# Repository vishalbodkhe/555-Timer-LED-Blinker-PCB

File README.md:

# 555 Timer LED Blinker PCB

A 555 Timer based LED Blinker PCB designed using KiCad.

## Project Overview

This project is a simple LED blinker circuit using the NE555 timer IC in astable mode.

The complete PCB design workflow was performed using KiCad, including:

- Circuit schematic design
- Footprint assignment
- PCB component placement
- PCB routing
- Design Rule Check (DRC)
- 3D PCB verification
- Gerber file generation
- Drill file generation

## Components

| Reference | Component | Value |
|----------|-----------|-------|
| U1 | NE555 Timer IC | NE555D |
| R1 | Resistor | 1kΩ |
| R2 | Resistor | 10kΩ |
| R3 | Resistor | 330Ω |
| C1 | Capacitor | 10µF |
| C2 | Capacitor | 100nF |
| D1 | LED | LED |
| J1 | Screw Terminal | 2-Pin |

## Circuit

The NE555 timer is configured in astable mode to generate a continuous square-wave output.

The output of the 555 timer drives the LED through a 330Ω current-limiting resistor.

## Design Workflow

1. Schematic Design
2. Assign PCB Footprints
3. PCB Component Placement
4. PCB Routing
5. Design Rule Check
6. 3D PCB Verification
7. Gerber Generation
8. Drill File Generation

## PCB Design

The PCB was designed and routed using KiCad.

The board includes:

- 2-pin power input
- NE555 timer IC
- Timing resistor network
- Timing capacitors
- LED indicator
- Current limiting resistor
- Four mounting holes

## 3D PCB View

## Design Verification

- Schematic completed
- PCB layout completed
- PCB routing completed
- DRC completed successfully
- DRC Violations: 0
- Unconnected Items: 0
- 3D PCB model verified

## Gerber Files

Gerber files required for PCB fabrication are included in this repository.

Included fabrication files:

- Front Copper
- Back Copper
- Front Solder Mask
- Back Solder Mask
- Front Silkscreen
- Back Silkscreen
- Edge Cuts
- Drill Files

## Project Files

### KiCad Files

- `p2.kicad_sch` — Schematic
- `p2.kicad_pcb` — PCB Layout
- `p2.kicad_pro` — KiCad Project

### Manufacturing Files

- `p2-F_Cu.gbr`
- `p2-B_Cu.gbr`
- `p2-F_Mask.gbr`
- `p2-B_Mask.gbr`
- `p2-F_Silkscreen.gbr`
- `p2-B_Silkscreen.gbr`
- `p2-Edge_Cuts.gbr`
- `p2-PTH.drl`
- `p2-NPTH.drl`

## Tools Used

- KiCad
- PCB Editor
- Schematic Editor
- 3D Viewer
- Design Rules Checker
- Gerber Viewer

## Learning Outcomes

Through this project, I learned and practiced:

- PCB schematic creation
- Electronic component selection
- Footprint assignment
- PCB layout design
- Component placement
- PCB trace routing
- Ground plane / copper zone
- Design Rule Checking
- Gerber generation
- Drill file generation
- 3D PCB visualization

## Project Status

**Completed**

Schematic → PCB Layout → Routing → DRC → 3D Verification → Gerber Generation

## Author

**Vishal Bodkhe**

Electronics & Computer Engineering

## License

This project is created for educational and portfolio purposes.

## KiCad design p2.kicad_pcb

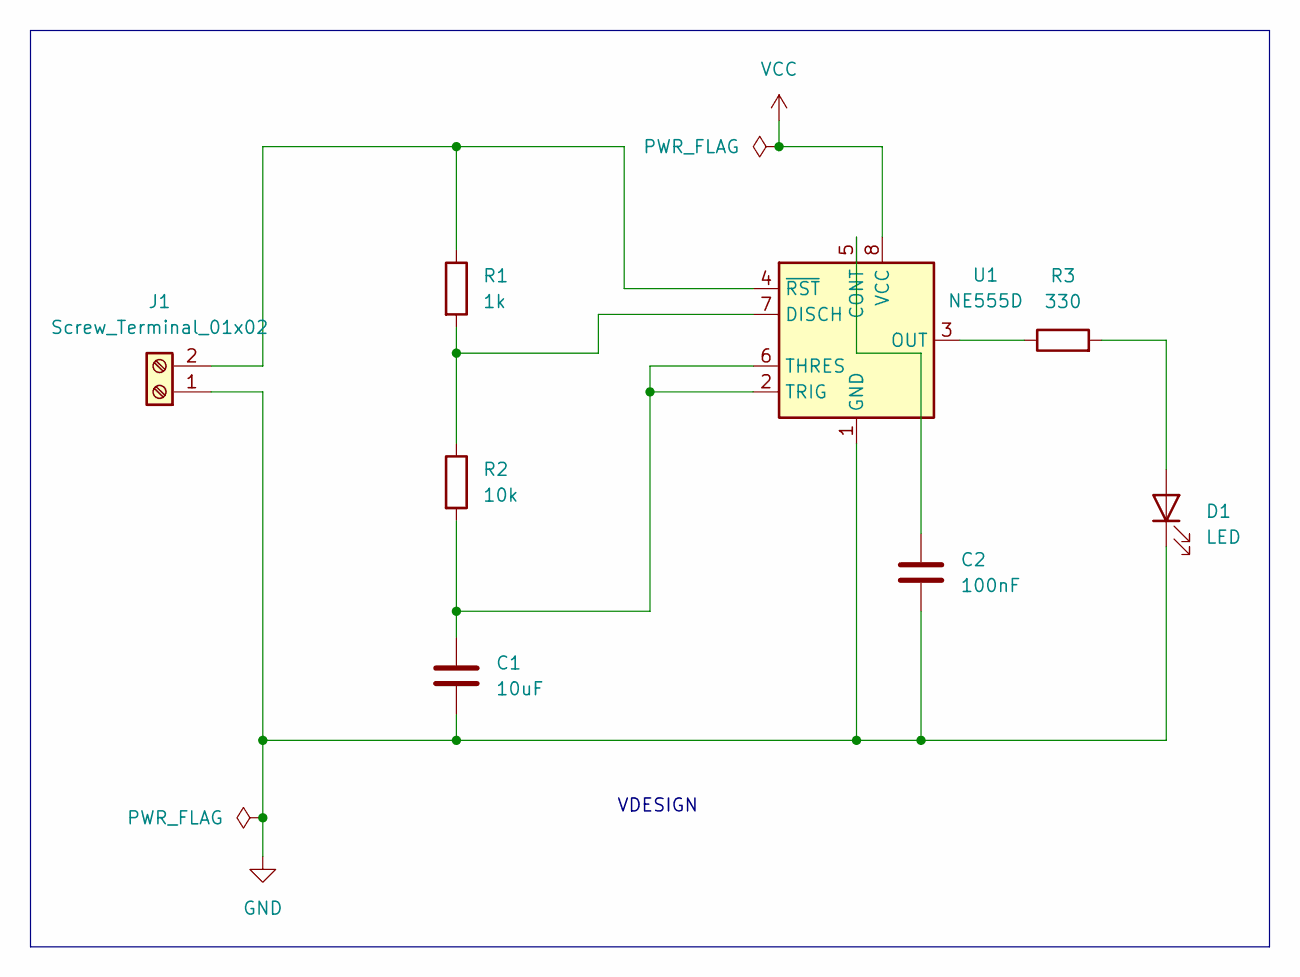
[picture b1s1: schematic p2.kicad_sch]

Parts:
C1: 10uF; C_0805_2012Metric
C2: 100nF; C_0805_2012Metric
D1: LED; LED_D5.0mm
J1: Screw_Terminal_01x02; Altech_AK100_1x02_P5.00mm
R1: 1k; R_0805_2012Metric
R2: 10k; R_0805_2012Metric
R3: 330; R_0805_2012Metric
U1: NE555D; SOIC-8_3.9x4.9mm_P1.27mm

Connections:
GND: C1.2, C2.2, D1.1 (K), J1.1, U1.1 (GND)
unnamed: D1.2 (A), R3.2
unnamed: J1.2, R1.1, U1.4 (~RST)
unnamed: C2.1, U1.5 (CONT)
unnamed: R1.2, R2.1, U1.7 (DISCH)
unnamed: R3.1, U1.3 (OUT)
unnamed: C1.1, R2.2, U1.2 (TRIG), U1.6 (THRES)
VCC: U1.8 (VCC)

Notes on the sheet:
VDESIGN

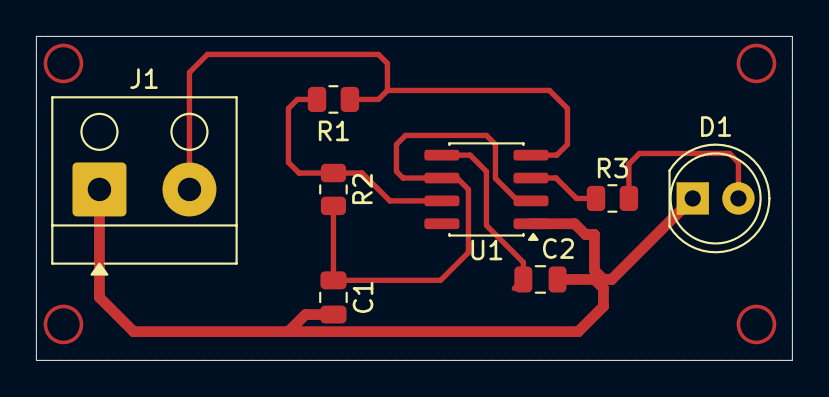
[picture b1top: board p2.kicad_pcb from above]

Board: 2 copper layers, 42.0 x 18.0 mm, 8 parts (0 on the bottom side), 7 nets.
